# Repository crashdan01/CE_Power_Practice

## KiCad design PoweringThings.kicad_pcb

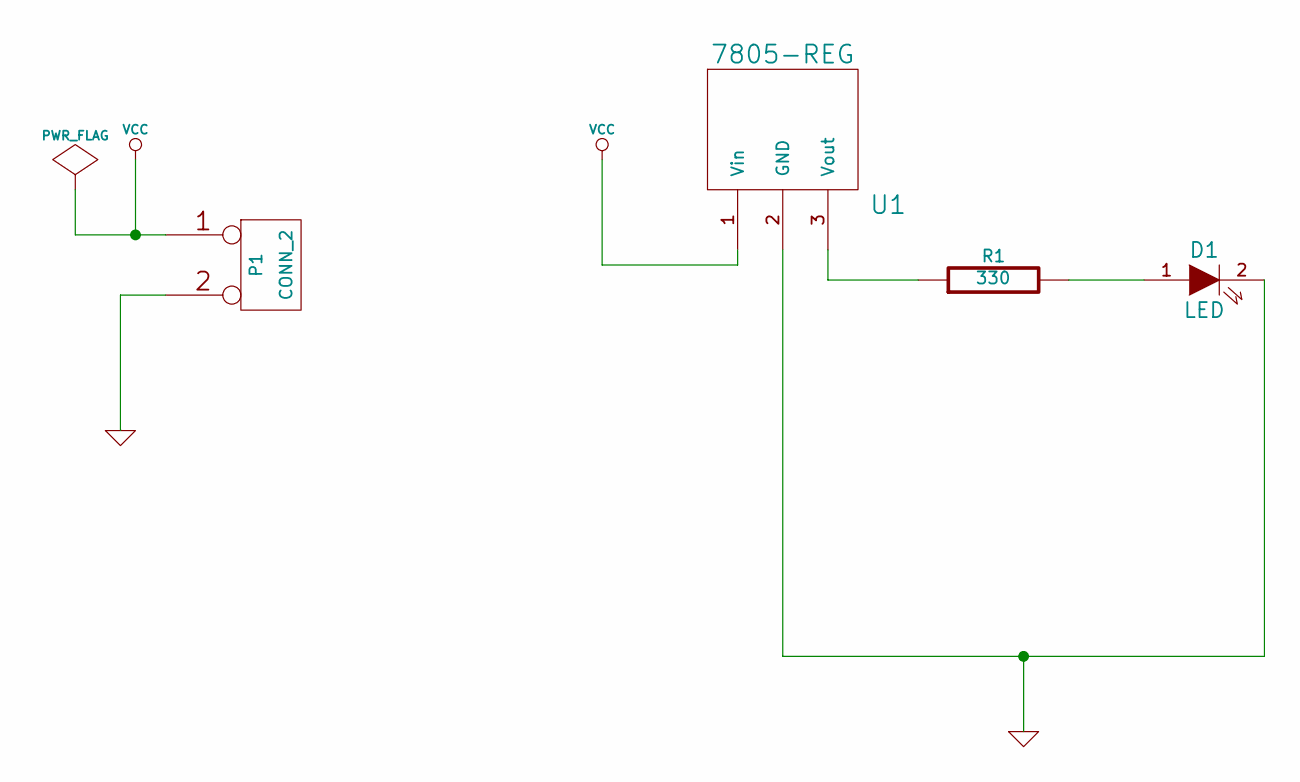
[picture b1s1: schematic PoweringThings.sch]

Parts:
D1: LED
P1: CONN_2
R1: 330
U1: 7805-REG

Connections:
GND: D1.2 (K), P1.2 (PM), U1.2 (GND)
unnamed: R1.1, U1.3 (Vout)
unnamed: D1.1 (A), R1.2
VCC: P1.1, U1.1 (Vin)

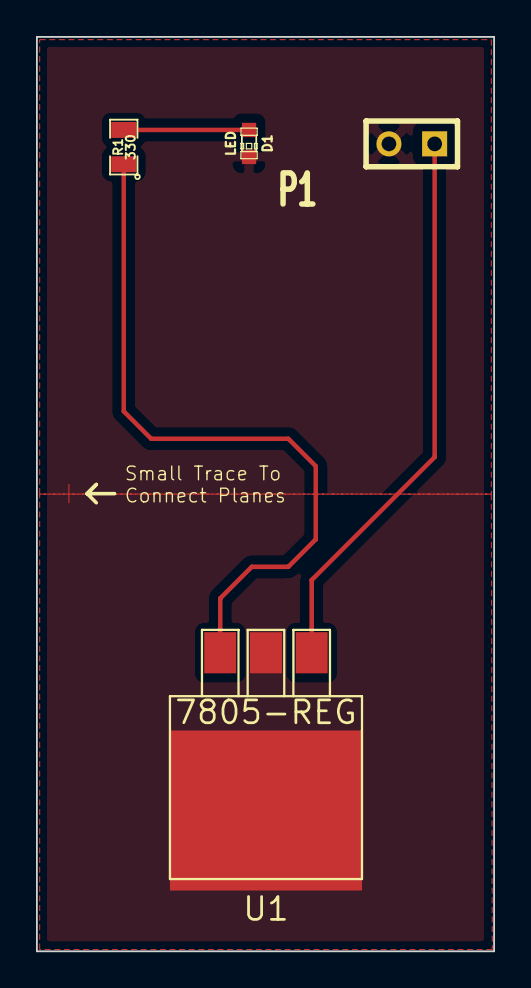
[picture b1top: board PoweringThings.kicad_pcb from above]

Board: 2 copper layers, 25.4 x 50.8 mm, 4 parts (0 on the bottom side), 4 nets.

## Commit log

2014-01-29 Ready to play with
    This has a dummy circuit built on it, with a large voltage regulator at
    the bottom, needing to be soldered to a copper area with the "SOLID"
    property, that will act as a heat sink. The question is, how do you
    join it with the copper pour at the top, that has the area property of
    "THERMAL RELIEF"? If they don't physically connect, then the GROUND
    connection of the voltage regulator has no path.
2014-01-29 Added GND plane "Priority" property
    I now have to GND planes, both on the front side copper. The upper
    plane, is set to priority "2", and the bottom is set to priority "1".
    The upper is set to thermal relief (check the ground pad on the pin
    header, upper right), and the bottom is set to solid, to ensure full
    contact with the thermal pad on the DPAK3 package. Even though this
    would result in a fully conductive surface in reality, you have to add a
